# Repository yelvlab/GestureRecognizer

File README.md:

# GestureRecognizer
Arduino gesture recognizer 

**Arduino Micro & APDS-9960**

# 项目进展预览：

- 测试版v0.1

# 项目介绍：

- 灵感来源：[项目分享| 仅79行代码完成创意无限的手势识别-达尔闻](https://mp.weixin.qq.com/s/ycUFOZZUidfz-ktJOUYYWw)

- 驱动库：[SparkFun APDS-9960](https://github.com/sparkfun/SparkFun_APDS-9960_Sensor_Arduino_Library)

# 文件介绍：

## CADs 目录:

- `keep_out.dwg`

PCB 边框切割以及螺丝孔文件

- `acrylic_cut.dwg`

亚克力外壳切割文件

## PCB工程目录：

- `GestureRecongnition_vx.x`目录

开源PCB工具`KiCAD`项目工程文件，`vx.x`为版本号

`v0.x`为测试版本

## Docs目录：

- `APDS9960.pdf`

`APDS-9960`模组数据手册

- `arduino_micro_schematic.pdf`

Arduino Micro 开发板原理图文件

- `atmel-atmega16u4-32u4_datasheet.pdf`

ATMEL公司`ATMEGA32U4`芯片数据手册

- `SPX3819-3.3.pdf`

`SPX3819` LDO指定输出3.3V芯片手册

## Pics目录：

- `view_F.jpg`:

PCB 3D预览顶视图

- `view_B.jpg`:

PCB 3D预览底视图

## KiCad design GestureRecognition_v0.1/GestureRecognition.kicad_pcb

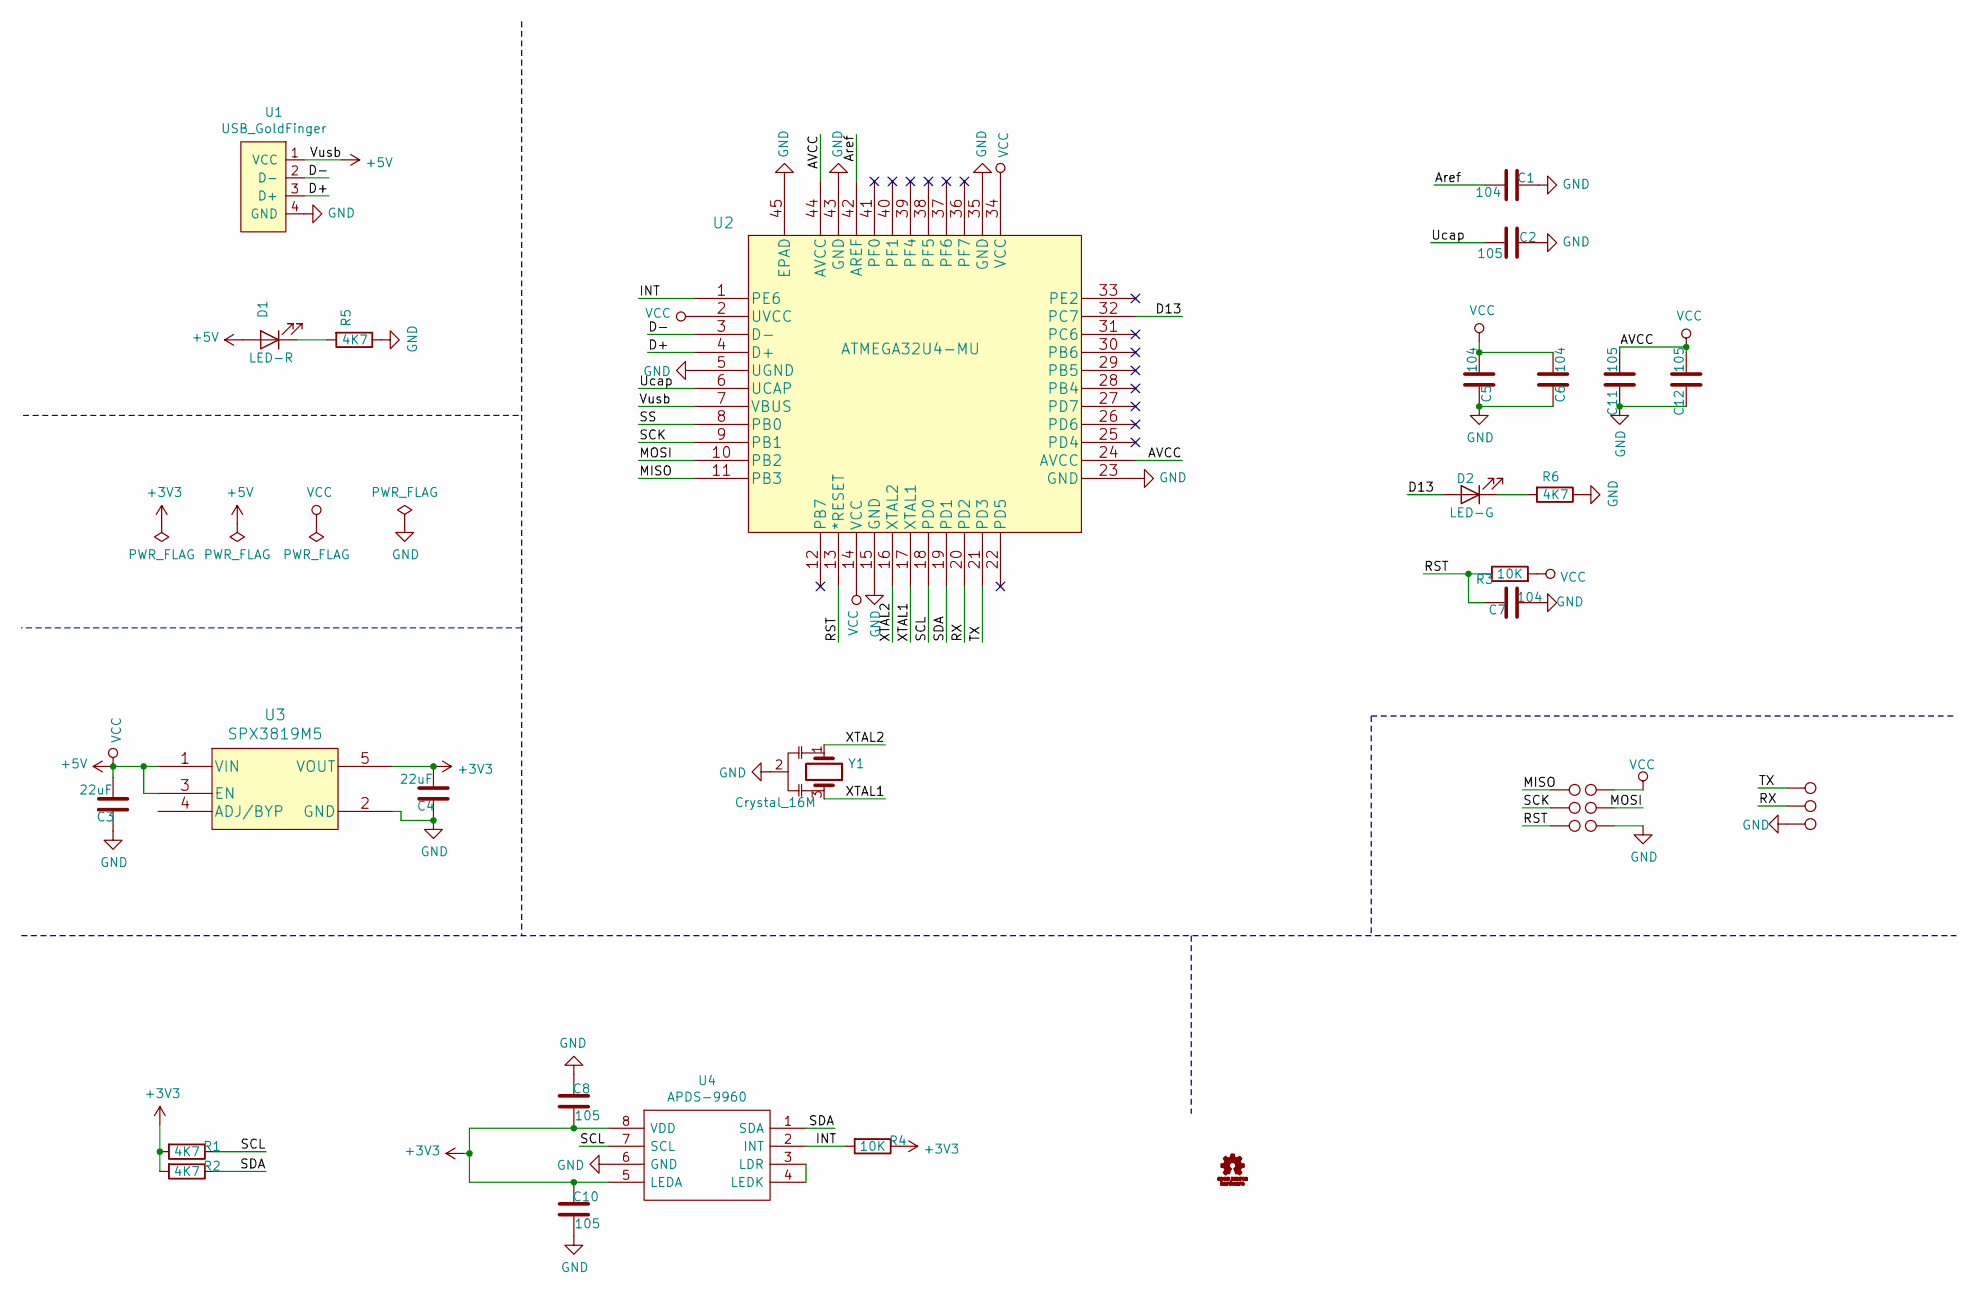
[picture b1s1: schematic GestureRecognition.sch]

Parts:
C1, C5, C6, C7: 104; C0402
C2, C8, C10, C11, C12: 105; C0402
C3, C4: 22uF; C0805
D1: LED-R; LED_0603_1608Metric_Castellated
D2: LED-G; LED_0603_1608Metric_Castellated
R1, R2, R5, R6: 4K7; R0402
R3, R4: 10K; R0402
TP1, TP2, TP3, TP4, TP5, TP6, TP7, TP8, TP9: TestPoint; TestPoint_Pad_D1.0mm
U1: USB_GoldFinger; USB-kingfigure
U2: ATMEGA32U4-MU
U3: SPX3819M5; SPX3819M5-L-3-3&slash_TR
U4: APDS-9960; APDS-9950; Manufacturer_Part_Number APDS-9960; Mouser Part Number 630-APDS-9960
Y1: Crystal_16M; CSTCE16M

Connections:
+3V3: C4.2, C8.2, C10.1, R1.2, R2.2, R4.1, U3.5 (VOUT), U4.5 (LEDA), U4.8 (VDD)
+5V: C3.2, C5.2, C6.2, C11.2, C12.2, D1.2 (A), R3.2, TP5.1, U1.1 (VCC), U2.2 (UVCC), U2.7 (VBUS), U2.14 (VCC), U2.24 (AVCC), U2.34 (VCC), U2.44 (AVCC), U3.1 (VIN), U3.3 (EN)
/Aref: C1.2, U2.42 (AREF)
/D13: D2.2 (A), U2.32 (PC7)
/D+: U1.3 (D+), U2.4 (D+)
/D-: U1.2 (D-), U2.3 (D-)
/INT: R4.2, U2.1 (PE6), U4.2 (INT)
/MISO: TP4.1, U2.11 (PB3)
/MOSI: TP7.1, U2.10 (PB2)
/RST: C7.1, R3.1, TP8.1, U2.13 (*RESET); also elsewhere on the board
/RX: TP2.1, U2.20 (PD2)
/SCK: TP6.1, U2.9 (PB1)
/SCL: R1.1, U2.18 (PD0), U4.7 (SCL)
/SDA: R2.1, U2.19 (PD1), U4.1 (SDA)
/SS: U2.8 (PB0)
/TX: TP3.1, U2.21 (PD3)
/Ucap: C2.1, U2.6 (UCAP)
/XTAL1: U2.17 (XTAL1), Y1.3
/XTAL2: U2.16 (XTAL2), Y1.1
GND: C1.1, C2.2, C3.1, C4.1, C5.1, C6.1, C7.2, C8.1, C10.2, C11.1, C12.1, R5.1, R6.1, TP1.1, TP9.1, U1.4 (GND), U2.5 (UGND), U2.15 (GND), U2.23 (GND), U2.35 (GND), U2.43 (GND), U2.45 (EPAD), U3.2 (GND), U4.6 (GND), Y1.2; also elsewhere on the board
unnamed: D1.1 (K), R5.2
unnamed: D2.1 (K), R6.2
unnamed: U4.3 (LDR), U4.4 (LEDK)

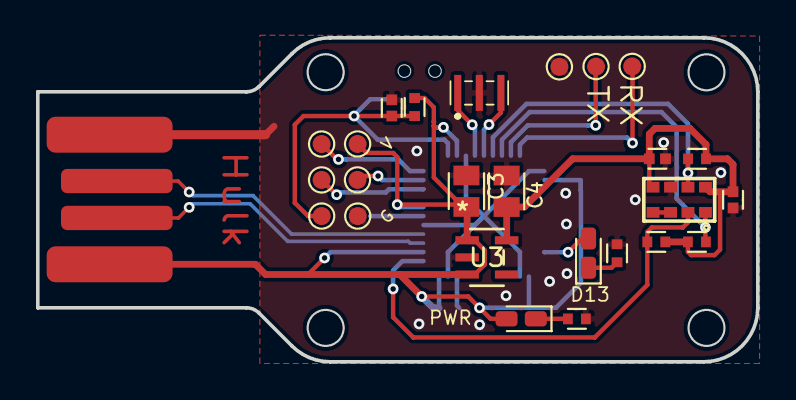
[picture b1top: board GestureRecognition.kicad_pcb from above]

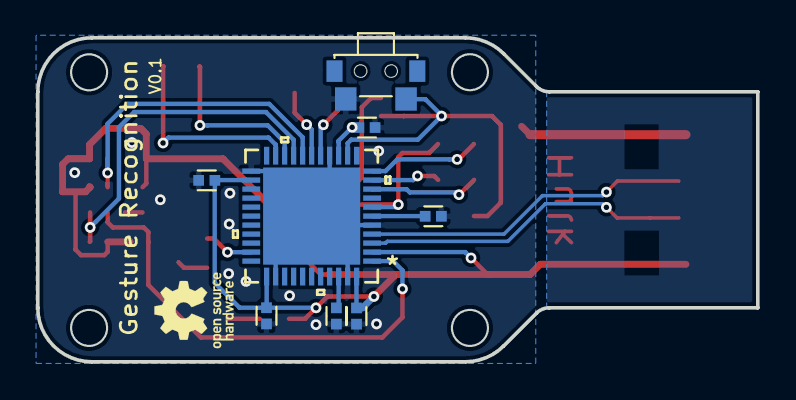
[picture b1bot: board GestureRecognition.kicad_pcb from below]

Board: 2 copper layers, 40.0 x 18.0 mm, 34 parts (8 on the bottom side), 22 nets.

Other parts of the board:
K1: TS-018_TS24CA

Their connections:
/RST: K1.2; also elsewhere on the board
GND: K1.1; also elsewhere on the board

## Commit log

2020-03-04 Init
2020-03-05 fix silk
2020-03-06 add cache

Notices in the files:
parts and their libraries:
Copyright 2016 Accelerated Designs. All rights reserved.
